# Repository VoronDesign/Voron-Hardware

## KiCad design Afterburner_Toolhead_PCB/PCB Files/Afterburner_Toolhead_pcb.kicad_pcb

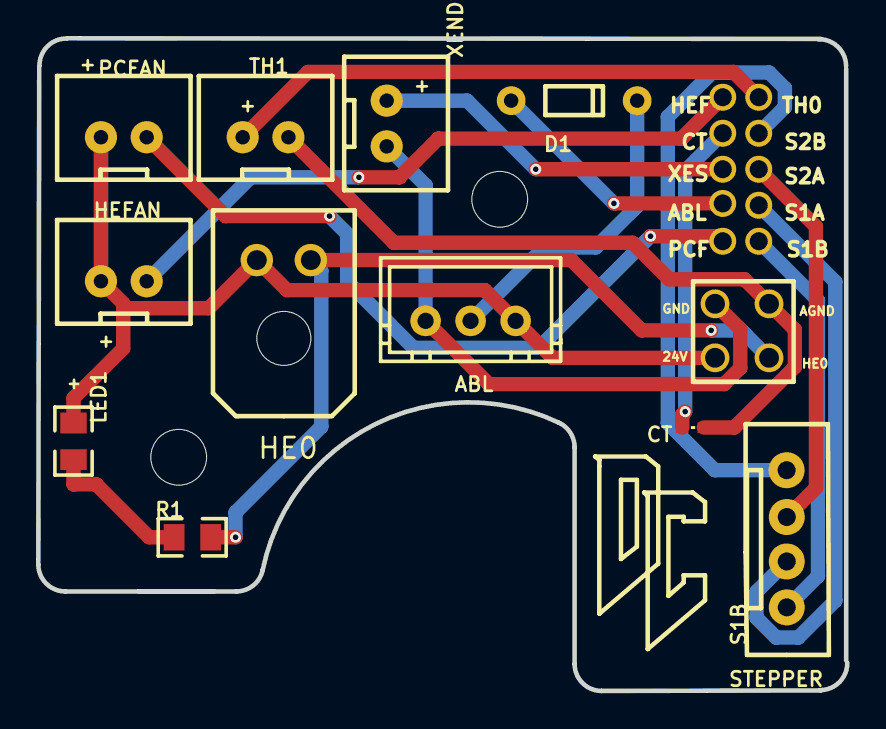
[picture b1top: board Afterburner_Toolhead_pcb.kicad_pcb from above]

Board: 2 copper layers, 44.9 x 36.3 mm, 13 parts (0 on the bottom side), 16 nets.

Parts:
ABL: ABL Sensor (Optional); JST-XH-03-PACKAGE-LONG-PAD
CT: Chamber Temp; 0402
D1: BAT85; DO-34_BD1.6-L3.0-P7.00-D0.6-RD
HE0: MicroFit_1x2; MICROFIT_2X1_WITHHOLE
HEFAN: +; JST-XH-02-ROUND_PAD
J1: MICROFIT-4; MICROFIT_2X2_NOHOLE
LED1: +; 0805-LED
PCFAN: +; JST-XH-02-ROUND_PAD
R1: 1.5K; RESISTOR 0805
STEPPER: S1B; JST-XH04
TH1: +; JST-XH-02-ROUND_PAD
U1: 2x5 2mm pitch; 2MM PITCH PS2 CONT 2X5
XENDSTOP: +; JST-XH-02-ROUND_PAD

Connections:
24V: ABL.1, HE0.2, HEFAN.1, J1.2, LED1.1, PCFAN.1
ABLSIGNALMCU: D1.2, U1.2
ABLSIGNALPROBE: ABL.2, D1.1
AGND: CT.2, J1.3, TH1.2
CHT: CT.1, U1.4
FAN2GND: PCFAN.2, U1.1
GND: ABL.3, J1.4, XENDSTOP.2
HEATER1GND: HE0.1, J1.1, R1.2
HEFANGND: HEFAN.2, U1.5
LED1_2: LED1.2, R1.1
STEPPER1A: STEPPER.3, U1.9
STEPPER1B: STEPPER.4, U1.10
STEPPER2A: STEPPER.2, U1.8
STEPPER2B: STEPPER.1, U1.7
TH1: TH1.1, U1.6
XENDSTOPSIGNAL: U1.3, XENDSTOP.1

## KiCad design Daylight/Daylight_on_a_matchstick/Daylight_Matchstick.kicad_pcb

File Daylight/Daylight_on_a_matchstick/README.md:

# Daylight on a matchstick

12 White leds to accurately illuminate your V0 or other ant-sized printer.

## BOM
| Quantity | Value                         | Package |
|----------|-------------------------------|---------|
|        4 | 100 Ohms Resistor             | 1210    |
|       12 | White LED (4000K, 90+ CRI)    | 2835    |
|        2 | JST-XH (2.54) angled connector| 2pin    |

## Changelog

### V1.0
Initial public release.

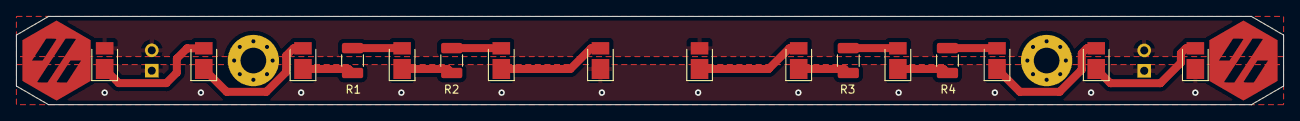
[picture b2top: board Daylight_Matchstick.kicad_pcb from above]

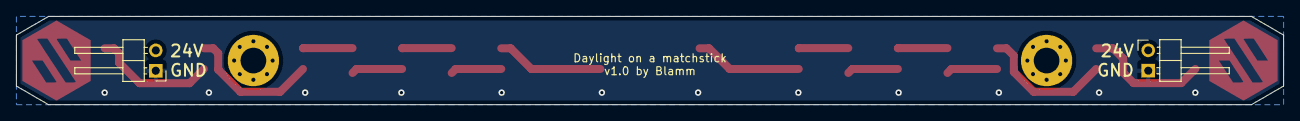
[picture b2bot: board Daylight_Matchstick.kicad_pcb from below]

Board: 2 copper layers, 158.0 x 11.0 mm, 20 parts (2 on the bottom side), 16 nets.

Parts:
D1, D2, D3, D4, D5, D6, D7, D8, D9, D10, D11, D12: LED_ALT; LED_PLCC_2835_Handsoldering
H1, H2: MountingHole; MountingHole_3.2mm_M3_Pad_Via
J1: Conn_01x02_Female; PinHeader_1x02_P2.54mm_Horizontal_mirrored
J2: Conn_01x02_Female; PinHeader_1x02_P2.54mm_Horizontal
R1, R2, R3, R4: 100R 0.5W; R_1210_3225Metric_Pad1.30x2.65mm_HandSolder

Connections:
+24V: D1.2 (A), D7.2 (A), J1.2, J2.2
GND: D6.1 (K), D12.1 (K), J1.1, J2.1
unnamed: D1.1 (K), D2.2 (A)
unnamed: D2.1 (K), D3.2 (A)
unnamed: D3.1 (K), R1.2
unnamed: D4.1 (K), R2.2
unnamed: D4.2 (A), R1.1
unnamed: D5.1 (K), D6.2 (A)
unnamed: D5.2 (A), R2.1
unnamed: D7.1 (K), D8.2 (A)
unnamed: D8.1 (K), R3.2
unnamed: D9.1 (K), R4.2
unnamed: D9.2 (A), R3.1
unnamed: D11.1 (K), D12.2 (A)
unnamed: D10.1 (K), D11.2 (A)
unnamed: D10.2 (A), R4.1

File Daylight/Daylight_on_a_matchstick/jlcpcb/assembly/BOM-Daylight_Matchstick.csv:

Comment,Designator,Footprint,LCSC
100R 0.5W,"R1,R2,R3,R4",R_1210_3225Metric_Pad1.30x2.65mm_HandSolder,C137089
LED_ALT,"D1,D10,D11,D12,D2,D3,D4,D5,D6,D7,D8,D9",LED_PLCC_2835_Handsoldering,C182223
MountingHole,H2,MountingHole_3.2mm_M3_Pad_Via,
MountingHole,H1,MountingHole_3.2mm_M3_Pad_Via,
Conn_01x02_Female,J1,PinHeader_1x02_P2.54mm_Horizontal_mirrored,
Conn_01x02_Female,J2,PinHeader_1x02_P2.54mm_Horizontal,

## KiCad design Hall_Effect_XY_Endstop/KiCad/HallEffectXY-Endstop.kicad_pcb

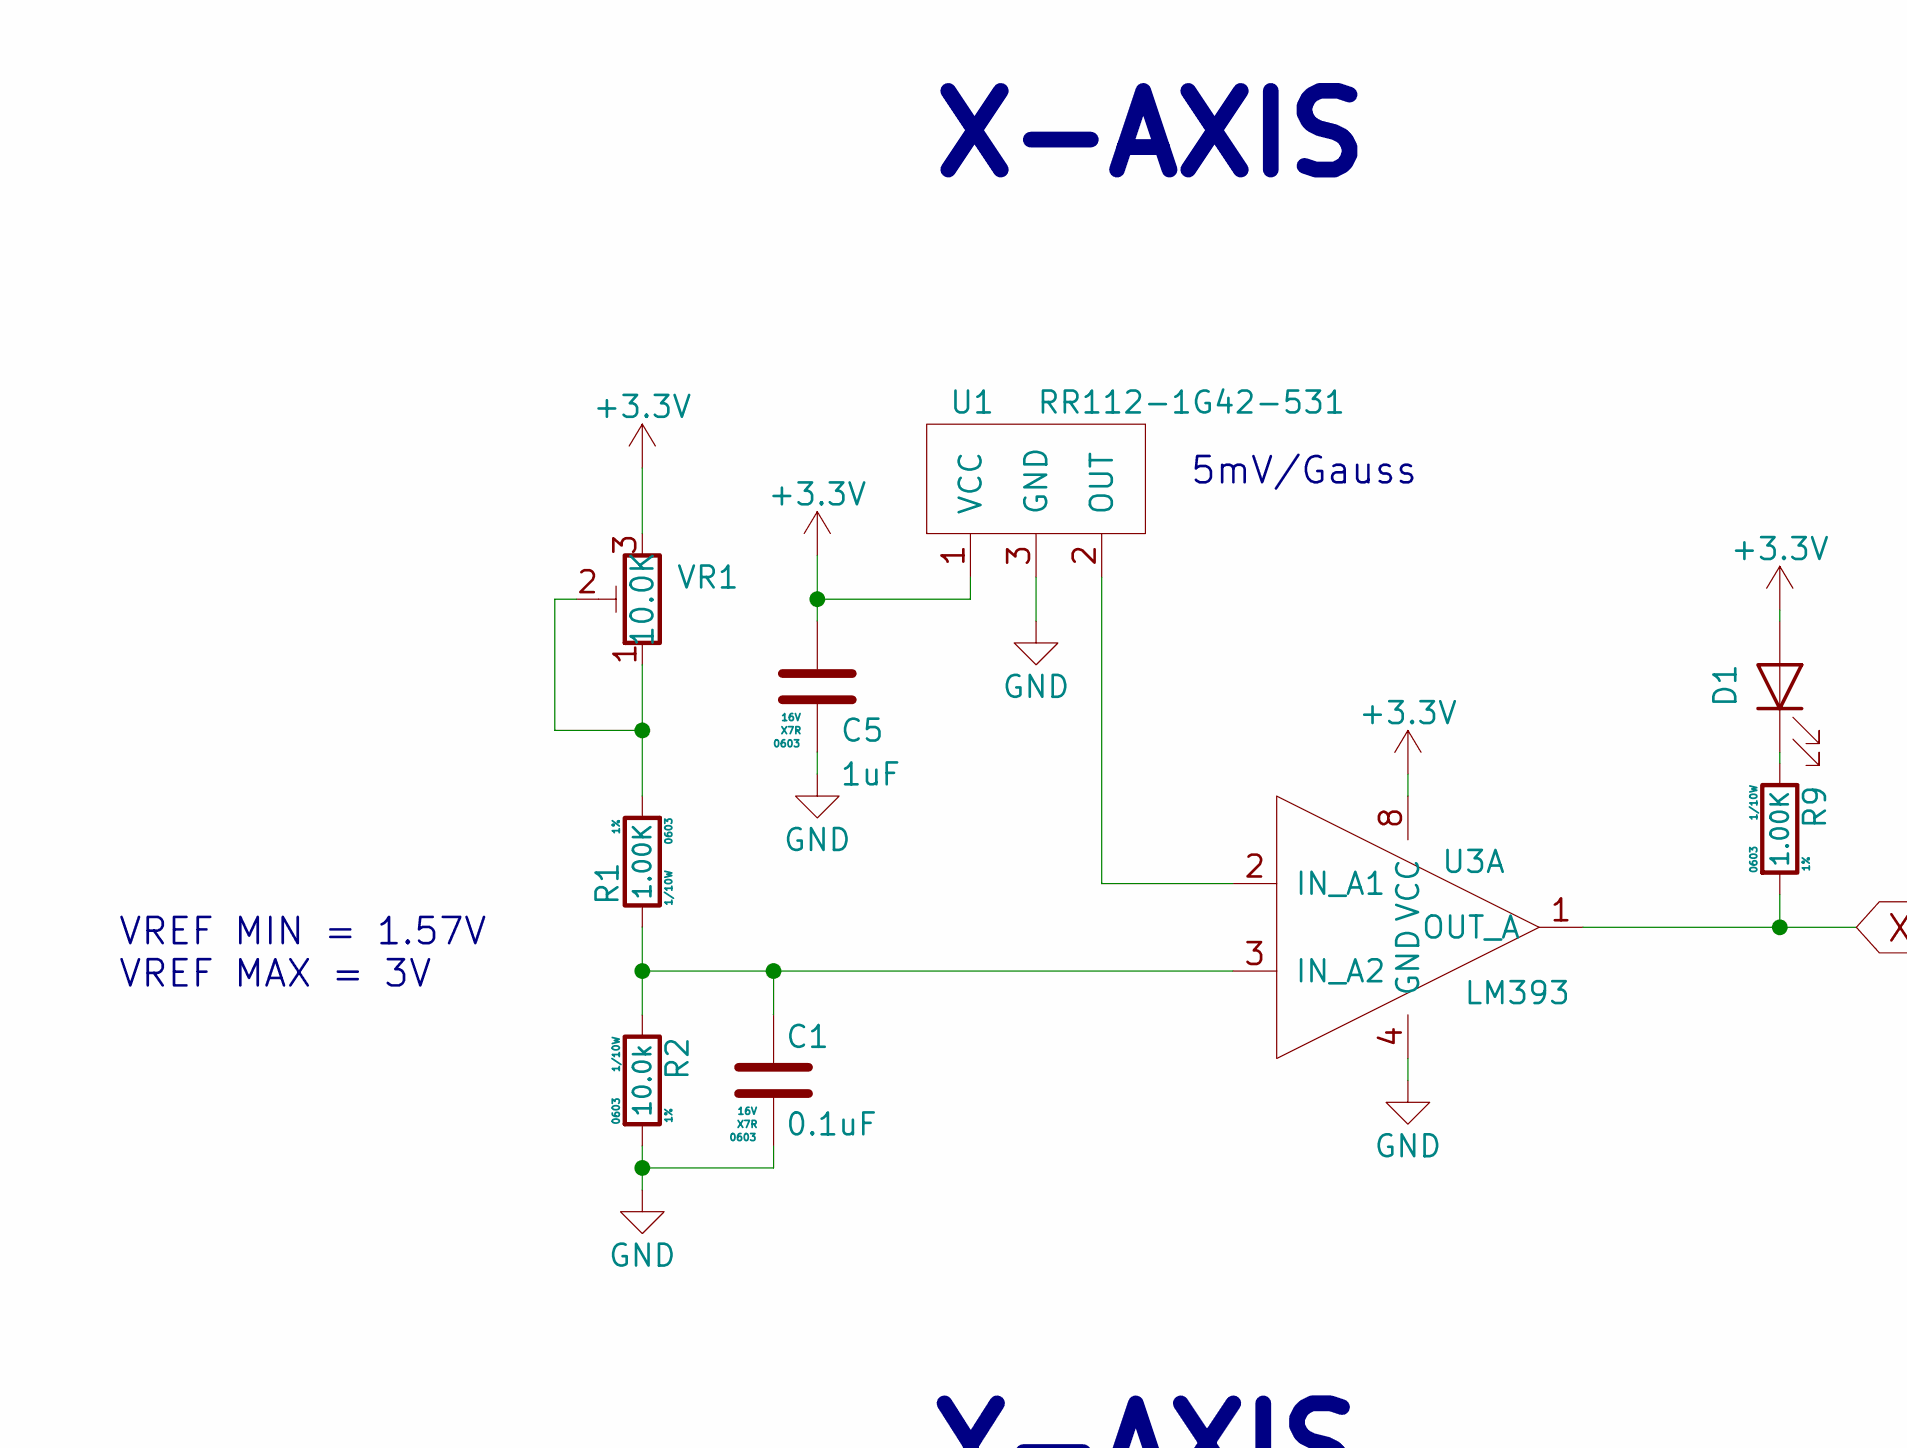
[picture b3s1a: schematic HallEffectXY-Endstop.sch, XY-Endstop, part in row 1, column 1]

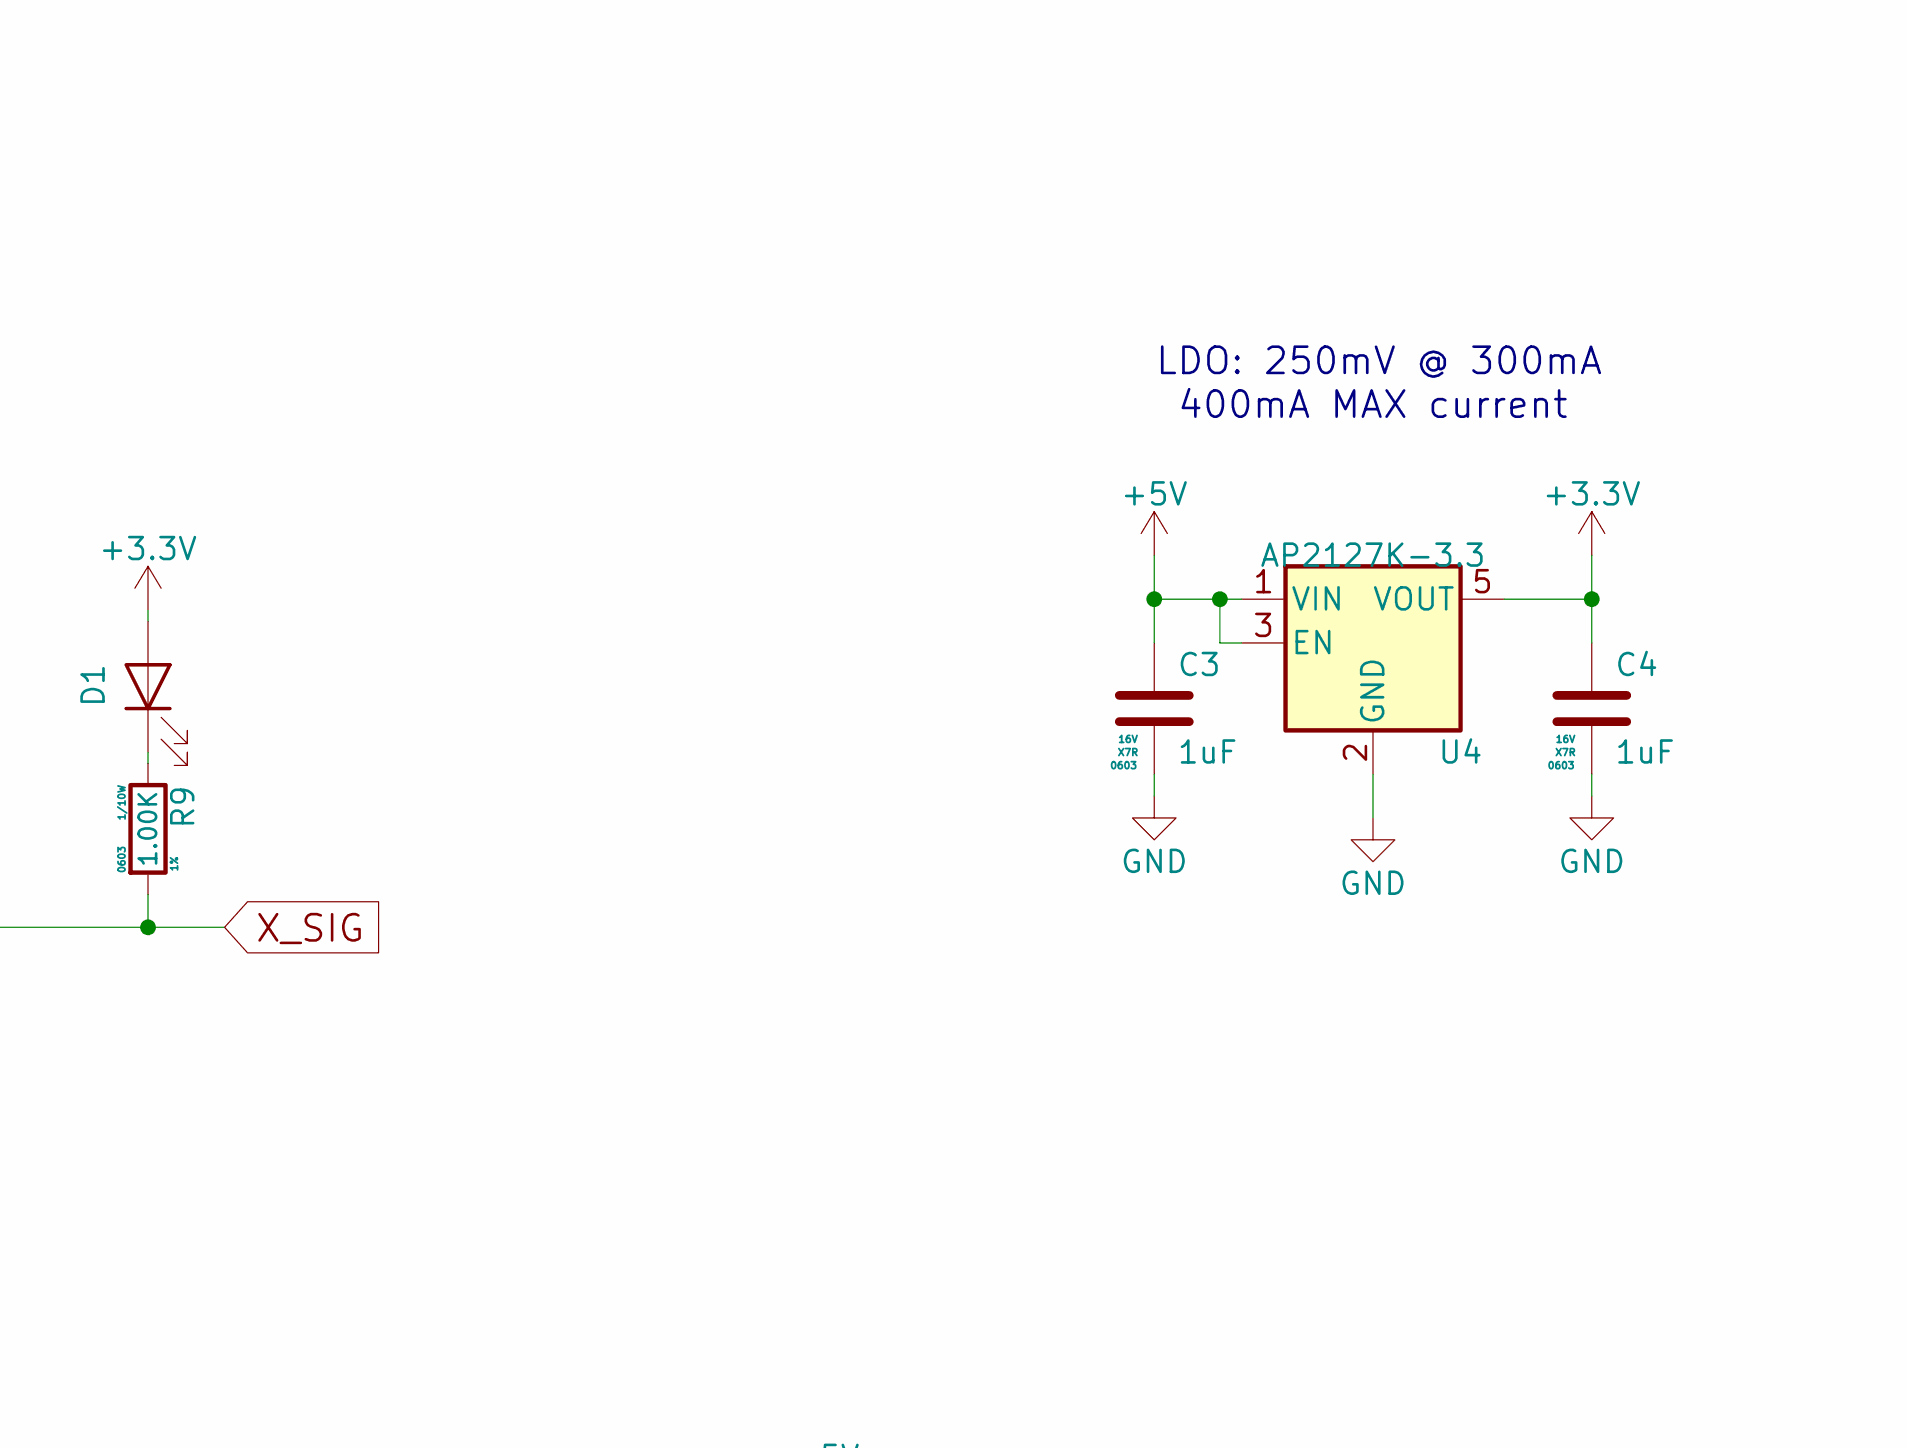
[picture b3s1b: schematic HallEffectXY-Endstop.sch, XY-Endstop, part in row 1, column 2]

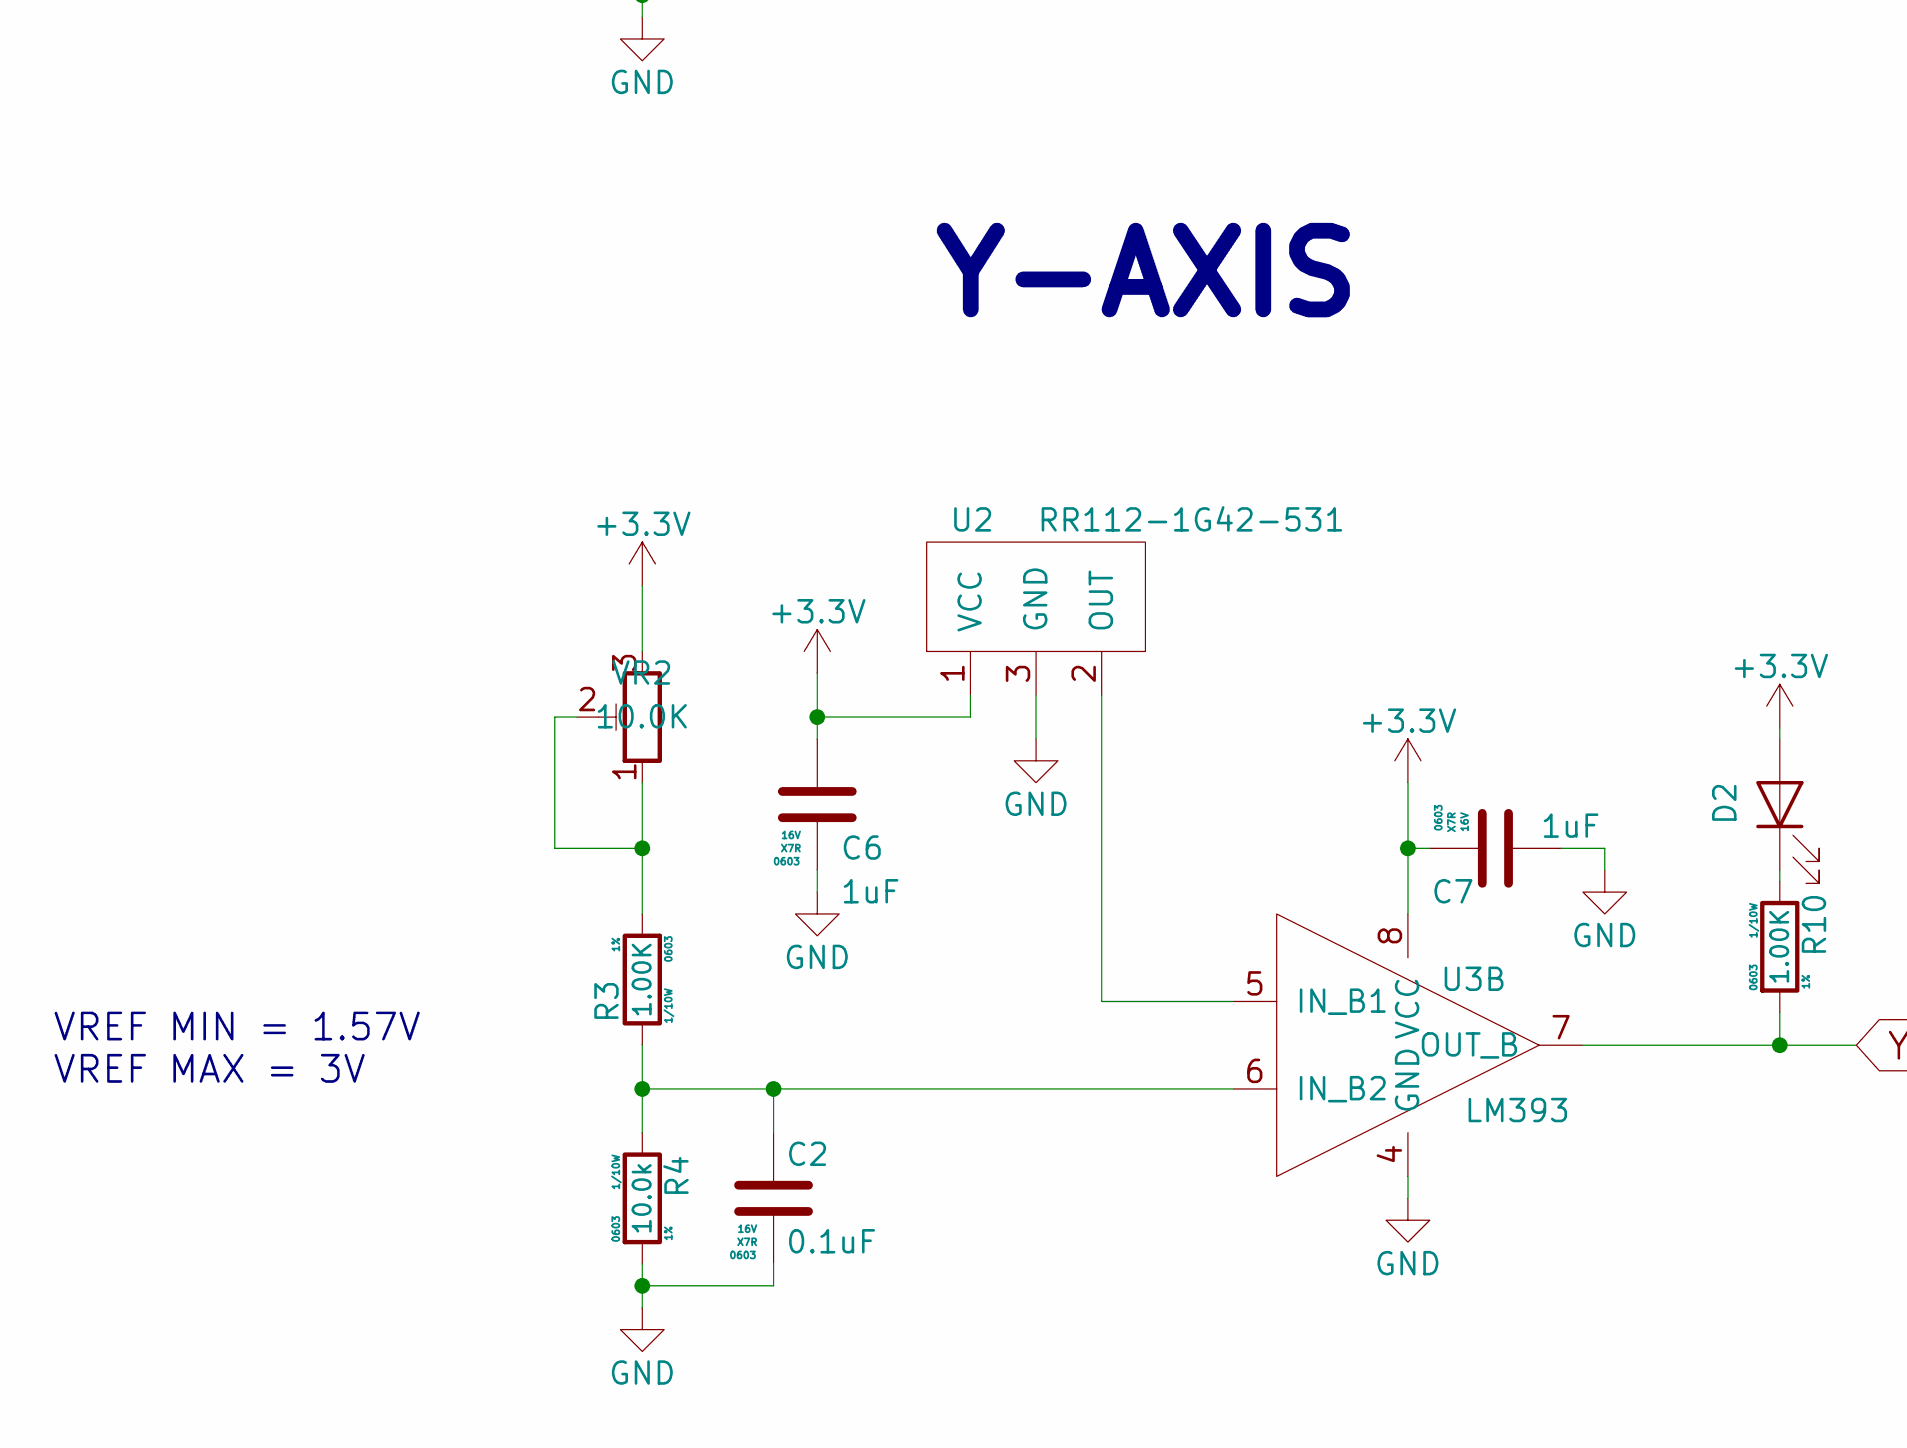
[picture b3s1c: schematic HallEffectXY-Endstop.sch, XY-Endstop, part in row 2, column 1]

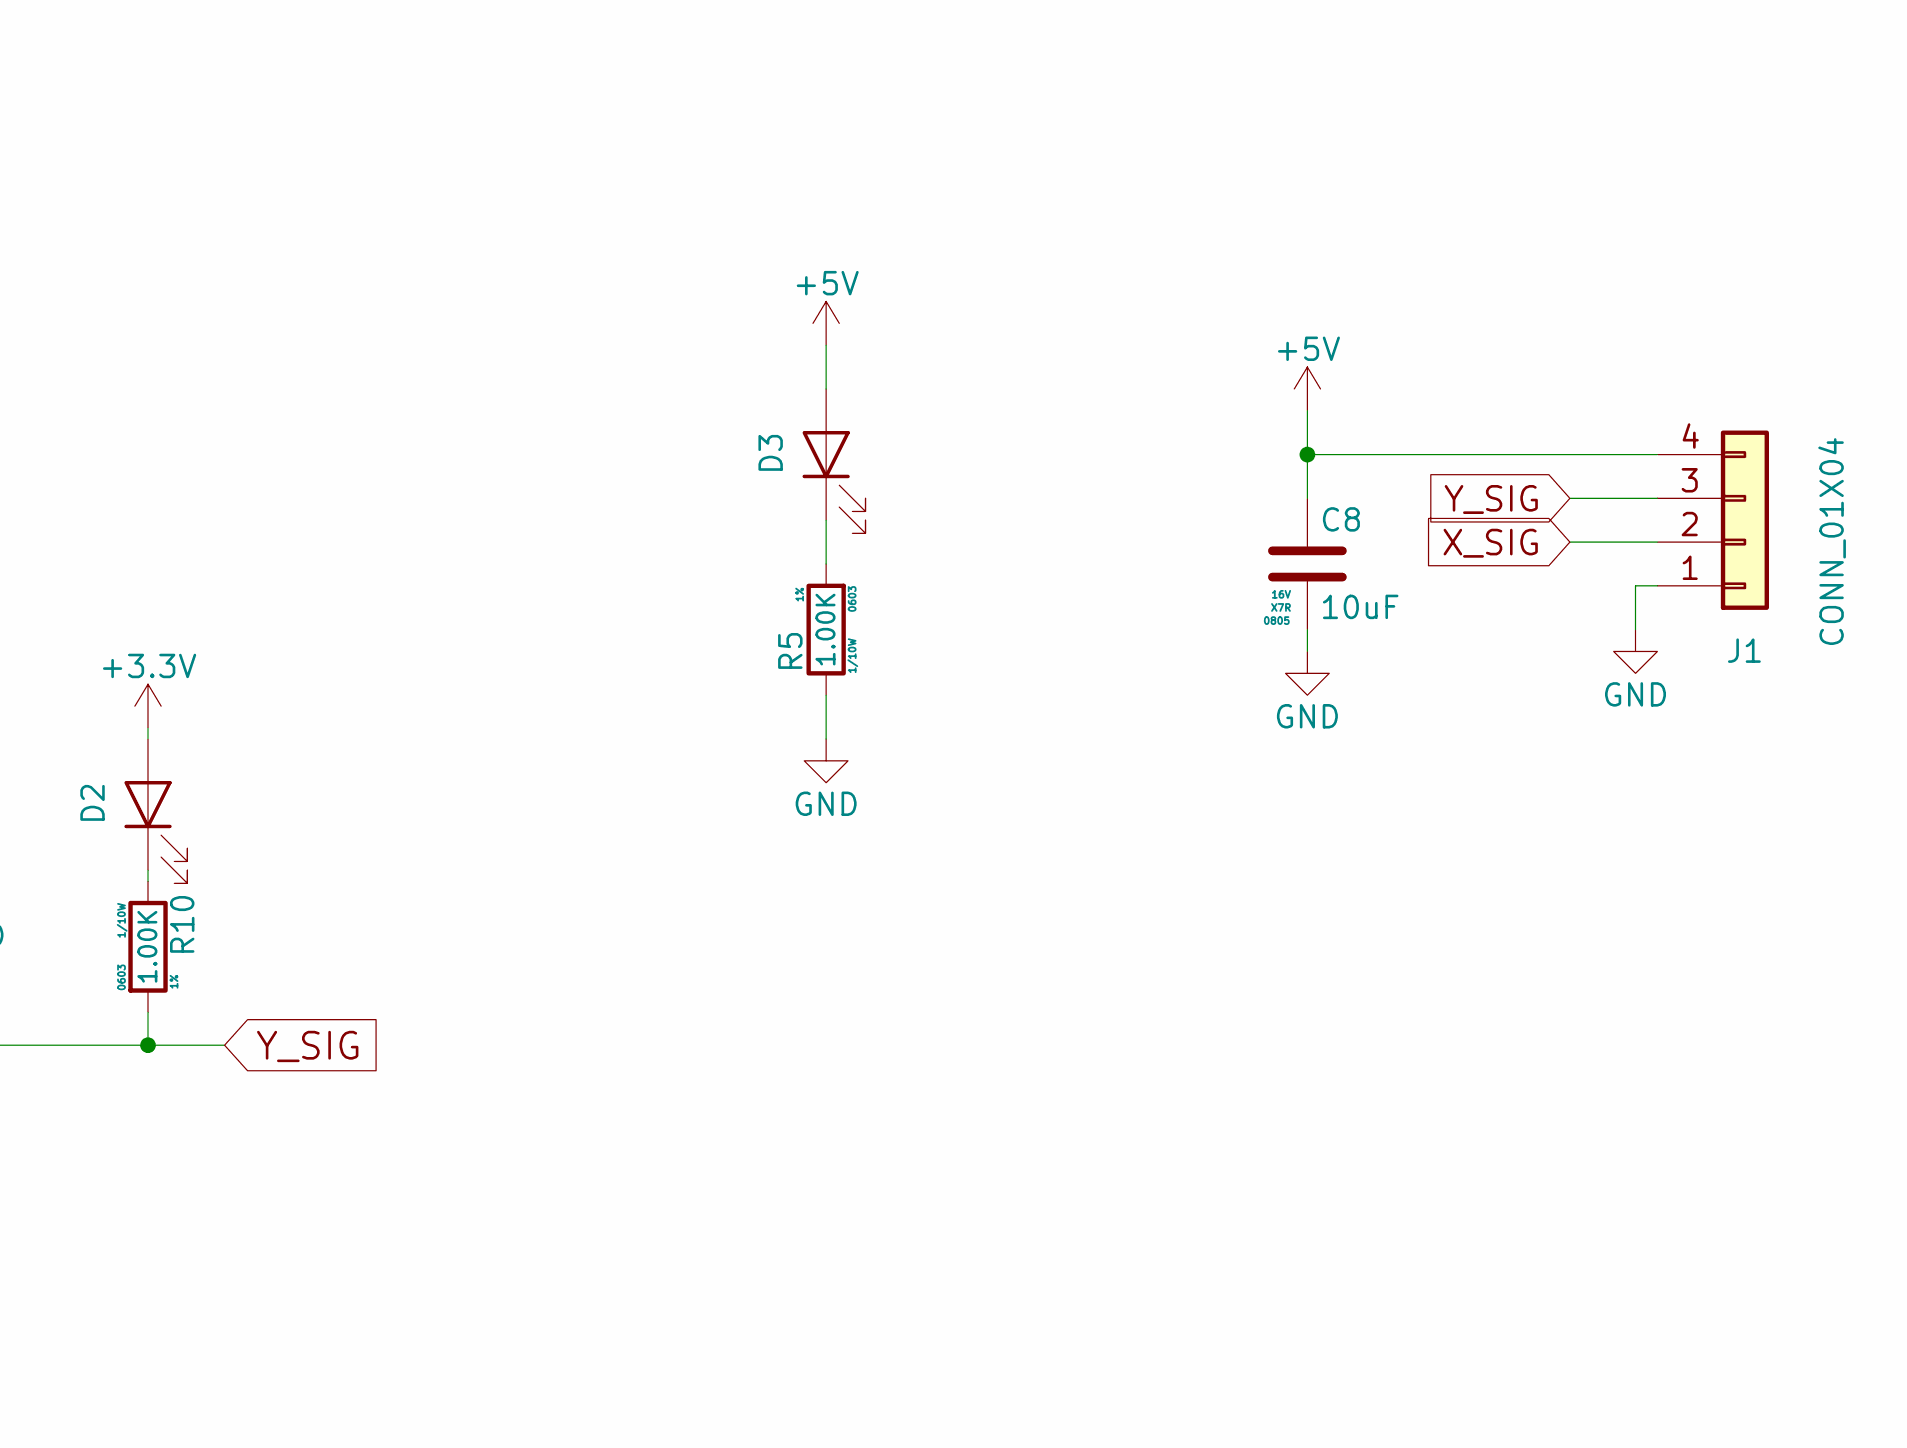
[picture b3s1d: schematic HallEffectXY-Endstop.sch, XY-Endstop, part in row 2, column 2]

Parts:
C1, C2: 0.1uF; C_0805_2012Metric; Voltage 16V; Manufacture P/N CC0603KRX7R7BB104; Digi-Key 311-1088-1-ND
C3, C4, C5, C6, C7: 1uF; C_0805_2012Metric; Voltage 16V; Manufacture P/N EMK107B7105KA-T; Digi-Key 587-1241-1-ND
C8: 10uF; C_0805_2012Metric; Voltage 16V; Manufacture P/N CL21A106KOQNNNG; Digi-Key 1276-6455-1-ND
D1, D2, D3: LED_0805; LED_0805_2012Metric; Manufacture P/N LS R976-NR-1; Digi-Key 475-1278-1-ND
J1: CONN_01X04; PinHeader_1x04_P2.54mm_Vertical; Manufacture P/N 0705530003; Digi-Key WM4902-ND
R1, R5: 1.00K; R_0805_2012Metric; Tolerance 1%; Manufacture P/N RC0402FR-071KL; Digi-Key 311-1.00KLRCT-ND
R2, R4: 10.0k; R_0805_2012Metric; Tolerance 1%; Manufacture P/N RC0603FR-0710KL; Digi-Key 311-10.0KHRCT-ND
R3, R9, R10: 1.00K; R_0805_2012Metric; Tolerance 1%; Manufacture P/N RC0603FR-071KL; Digi-Key 311-1.00KHRCT-ND
U1, U2: RR112-1G42-531; SOT-23; Manufacture P/N SS39ET; Digi-Key 306-RR112-1G42-531CT-ND
U3: LM393; SOIC-8_3.9x4.9mm_P1.27mm; Manufacture P/N LM393M; Digi-Key LM393MFS-ND
U4: AP2127K-3.3; SOT-23-5; Manufacture P/N AP2210N-3.3TRG1; Digi-Key AP2210N-3.3TRG1DICT-ND
VR1, VR2: 10.0K; CT6EP103; Manufacture P/N CT6EP103; Digi-Key CT6EP103-ND

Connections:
+3V3: C4.1, C5.1, C6.1, C7.2, D1.2 (A), D2.2 (A), U1.1 (VCC), U2.1 (VCC), U3.8 (VCC), U4.5 (VOUT), VR1.3, VR2.3
+5V: C3.1, C8.1, D3.2 (A), J1.4, U4.1 (VIN), U4.3 (EN)
GND: C1.2, C2.2, C3.2, C4.2, C5.2, C6.2, C7.1, C8.2, J1.1, R2.2, R4.2, R5.1, U1.3 (GND), U2.3 (GND), U3.4 (GND), U4.2 (GND)
unnamed: C1.1, R1.1, R2.1, U3.3 (IN_A2)
unnamed: C2.1, R3.1, R4.1, U3.6 (IN_B2)
unnamed: D1.1 (K), R9.1
unnamed: D2.1 (K), R10.1
unnamed: D3.1 (K), R5.2
unnamed: R1.2, VR1.1, VR1.2
unnamed: R3.2, VR2.1, VR2.2
unnamed: U1.2 (OUT), U3.2 (IN_A1)
unnamed: U2.2 (OUT), U3.5 (IN_B1)
X_SIG: J1.2, R9.2, U3.1 (OUT_A)
Y_SIG: J1.3, R10.2, U3.7 (OUT_B)

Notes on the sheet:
VREF MIN = 1.57V VREF MAX = 3V
X-AXIS
Y-AXIS
LDO: 250mV @ 300mA
400mA MAX current
5mV/Gauss

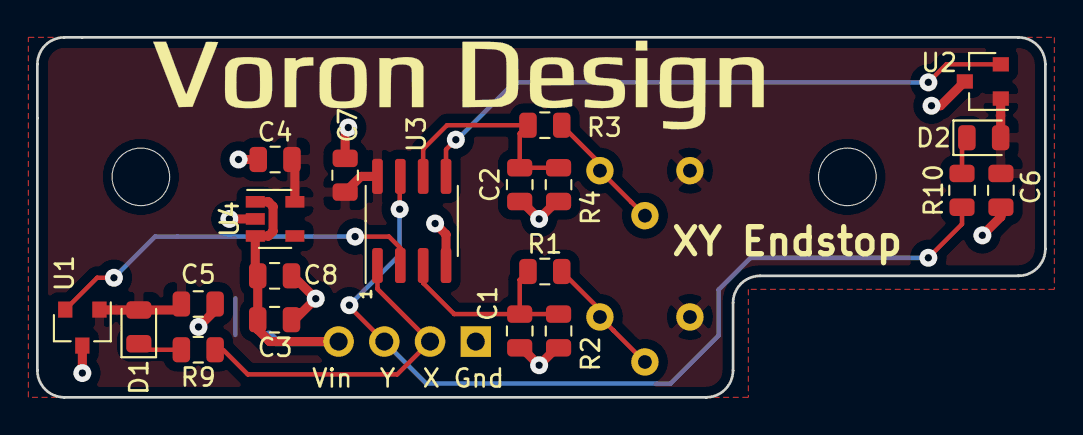
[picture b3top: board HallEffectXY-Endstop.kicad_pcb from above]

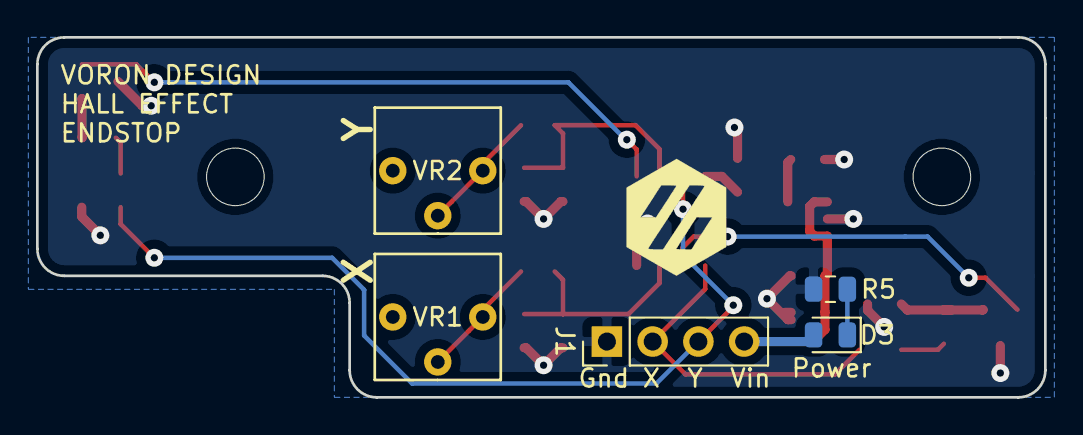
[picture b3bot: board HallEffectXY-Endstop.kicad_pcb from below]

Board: 2 copper layers, 56.0 x 20.0 mm, 25 parts (5 on the bottom side), 14 nets.

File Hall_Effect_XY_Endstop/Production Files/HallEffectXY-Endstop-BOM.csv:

Comment,Designator,Footprint,LCSC
0.1uF,"C2,C1",HallEffect_XY:C_0805_2012Metric,C49678
1uF,"C7,C6,C5,C3,C4",HallEffect_XY:C_0805_2012Metric,C28323
10uF,C8,HallEffect_XY:C_0805_2012Metric,C15850
LED_0805,"D2,D1,D3",HallEffect_XY:LED_0805_2012Metric,C84256
CONN_01X04,J1,HallEffect_XY:PinHeader_1x04_P2.54mm_Vertical,C225490
1.00K,"R1,R3,R9,R10,R5",HallEffect_XY:R_0805_2012Metric,C17513
10.0k,"R4,R2",HallEffect_XY:R_0805_2012Metric,C17414
SS39ET,"U2,U1",HallEffect_XY:SOT-23,C126669
LM393,U3,HallEffect_XY:SOIC-8_3.9x4.9mm_P1.27mm,C7955
AP2127K-3.3,U4,HallEffect_XY:SOT-23-5,C156285
10.0K,"VR2,VR1",HallEffect_XY:CT6EP103,C118956

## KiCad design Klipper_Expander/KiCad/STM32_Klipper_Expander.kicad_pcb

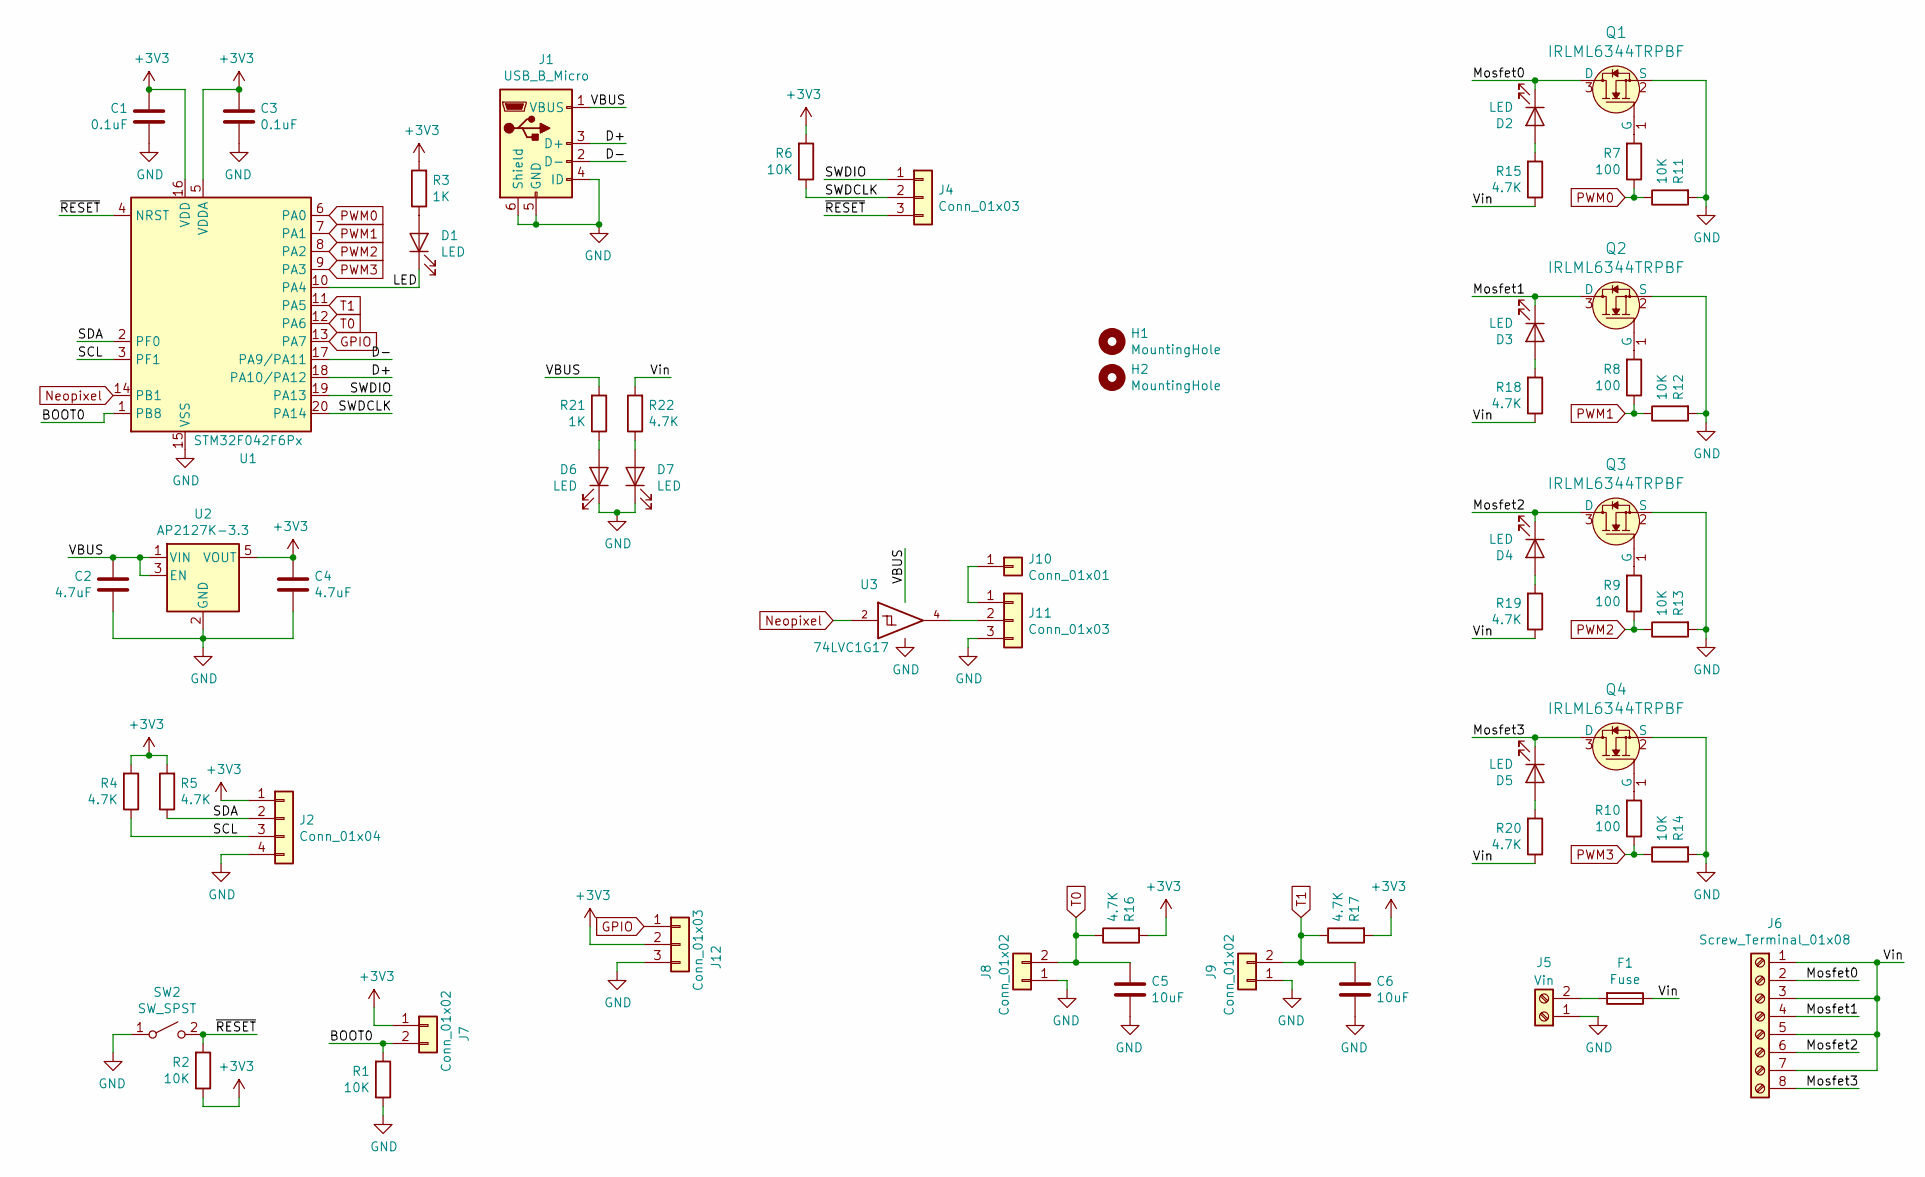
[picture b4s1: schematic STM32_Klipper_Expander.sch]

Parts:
C1, C3: 0.1uF; C_0805_2012Metric; MPN CC0805KRX7R9BB104; LCSC C49678
C2, C4: 4.7uF; C_0805_2012Metric; MPN CC0805KKX5R8BB475; LCSC C1779
C5, C6: 10uF; C_0805_2012Metric; MPN CC0805ZKY5V6BB106; LCSC C15850
D1, D2, D3, D4, D5, D6, D7: LED; LED_0805_2012Metric; MPN 17-215SURC/S530-A2/TR8; LCSC C84256
F1: Fuse; 3544-2_FuseHolder
H1, H2: MountingHole; MountingHole_3.2mm_M3
J1: USB_B_Micro; Molex-105017-0001-USBMicroB; MPN 1050170001
J2: Conn_01x04; PinHeader_1x04_P2.54mm_Vertical
J4, J11, J12: Conn_01x03; PinHeader_1x03_P2.54mm_Vertical
J5: Vin; 1x02_ScrewTerminal_Phoenix
J6: Screw_Terminal_01x08; 1x08_ScrewTerminal_Phoenix
J7, J8, J9: Conn_01x02; PinHeader_1x02_P2.54mm_Vertical
J10: Conn_01x01; PinHeader_1x01_P2.54mm_Vertical
Q1, Q2, Q3, Q4: IRLML6344TRPBF; SOT-23; MPN IRLML6344TRPBF; Digi-Key_PN IRLML6344TRPBFCT-ND
R1, R2, R6, R11, R12, R13, R14: 10K; R_0805_2012Metric; MPN RC0805JR-0710KL; LCSC C17414
R3, R21: 1K; R_0805_2012Metric; MPN RC0805JR-071KL; LCSC C17513
R4, R5, R15, R16, R17, R18, R19, R20, R22: 4.7K; R_0805_2012Metric; MPN RC0805JR-074K7L; LCSC C17673
R7, R8, R9, R10: 100; R_0805_2012Metric; MPN RC0805JR-07100RL; LCSC C17408
SW2: SW_SPST; 2PinTactileButton
U1: STM32F042F6Px; TSSOP-20_4.4x6.5mm_P0.65mm; MPN STM32F042F6P6; LCSC C81000
U2: AP2127K-3.3; SOT-23-5; MPN AP2127K-3.3TRG1; LCSC C156285
U3: 74LVC1G17; SOT-753; LCSC C6076

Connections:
+3V3: C1.2, C3.2, C4.2, J2.1, J7.1, J12.2, R2.1, R3.2, R4.2, R5.2, R6.2, R16.2, R17.2, U1.5 (VDDA), U1.16 (VDD), U2.5 (VOUT)
/BOOT0: J7.2, R1.2, U1.1 (PB8)
/D+: J1.3 (D+), U1.18 (PA10/PA12)
/D-: J1.2 (D-), U1.17 (PA9/PA11)
/LED: D1.1 (K), U1.10 (PA4)
/Mosfet0: D2.1 (K), J6.2, Q1.3 (D)
/Mosfet1: D3.1 (K), J6.4, Q2.3 (D)
/Mosfet2: D4.1 (K), J6.6, Q3.3 (D)
/Mosfet3: D5.1 (K), J6.8, Q4.3 (D)
/SCL: J2.3, R4.1, U1.3 (PF1)
/SDA: J2.2, R5.1, U1.2 (PF0)
/SWDCLK: J4.2, R6.1, U1.20 (PA14)
/SWDIO: J4.1, U1.19 (PA13)
/Vin: F1.1, J6.1, J6.3, J6.5, J6.7, R15.1, R18.1, R19.1, R20.1, R22.2
/~RESET: J4.3, R2.2, SW2.2 (B), U1.4 (NRST)
GND: C1.1, C2.1, C3.1, C4.1, C5.1, C6.1, D6.1 (K), D7.1 (K), J1.4 (ID), J1.5 (GND), J1.6 (Shield), J2.4, J5.1, J8.1, J9.1, J11.3, J12.3, Q1.2 (S), Q2.2 (S), Q3.2 (S), Q4.2 (S), R1.1, R11.2, R12.2, R13.2, R14.2, SW2.1 (A), U1.15 (VSS), U2.2 (GND), U3.3 (GND)
GPIO: J12.1, U1.13 (PA7)
Neopixel: U1.14 (PB1), U3.2
unnamed: D1.2 (A), R3.1
unnamed: D2.2 (A), R15.2
unnamed: D3.2 (A), R18.2
unnamed: D4.2 (A), R19.2
unnamed: D5.2 (A), R20.2
unnamed: D6.2 (A), R21.1
unnamed: D7.2 (A), R22.1
unnamed: F1.2, J5.2
unnamed: J10.1, J11.1
unnamed: J11.2, U3.4
unnamed: Q1.1 (G), R7.2
unnamed: Q2.1 (G), R8.2
unnamed: Q3.1 (G), R9.2
unnamed: Q4.1 (G), R10.2
PWM0: R7.1, R11.1, U1.6 (PA0)
PWM1: R8.1, R12.1, U1.7 (PA1)
PWM2: R9.1, R13.1, U1.8 (PA2)
PWM3: R10.1, R14.1, U1.9 (PA3)
T0: C5.2, J8.2, R16.1, U1.12 (PA6)
T1: C6.2, J9.2, R17.1, U1.11 (PA5)
VCC: C2.2, J1.1 (VBUS), R21.2, U2.1 (VIN), U2.3 (EN), U3.5 (VCC)

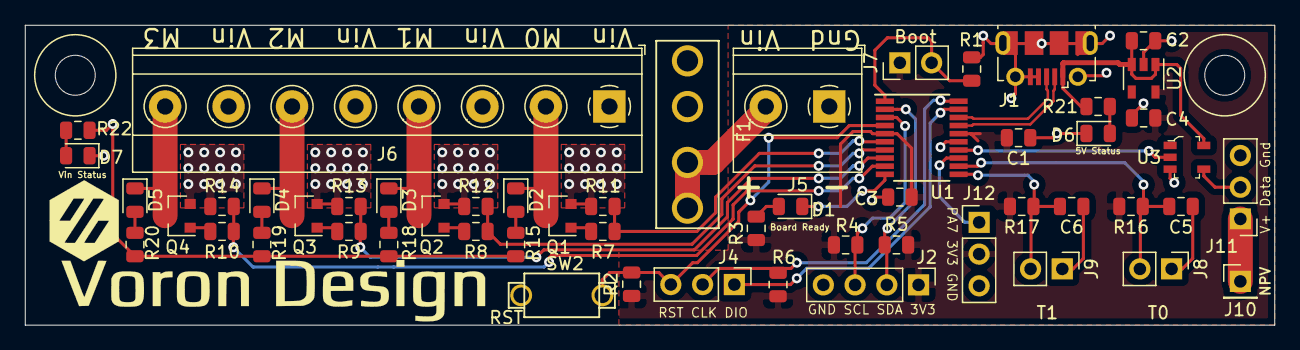
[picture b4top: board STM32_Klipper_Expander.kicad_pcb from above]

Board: 2 copper layers, 100.0 x 24.0 mm, 57 parts (0 on the bottom side), 39 nets.

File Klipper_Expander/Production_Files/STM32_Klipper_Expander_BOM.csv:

Comment,Qty,5 boards,Designator,MPN,Digikey PN,Footprint,LCSC
0.1uF,2,10,"C1,C3",CC0805KRX7R9BB104,311-1140-1-ND,0805,C49678
4.7uF,2,10,"C4,C2",CC0805KKX5R8BB475,311-1871-1-ND,0805,C1779
10uF,2,10,"C5,C6",CC0805ZKY5V6BB106 ,311-1355-1-ND,0805,C15850
LED,1,5,D1,17-215SURC/S530-A2/TR8 ,732-4984-1-ND,0805,C84256
Fuse,1,5,F1,?3544-2?,36-3544-2-ND,TRA_KiCad_Footprints:3544-2_FuseHolder,
MountingHole,2,10,"H1,H2",,,MountingHole:MountingHole_3.2mm_M3,
USB_B_Micro,1,5,J1,1050170001?,WM1399CT-ND,TRA_KiCad_Footprints:Molex-105017-0001-USBMicroB,
Conn_01x01,1,5,J10,PH1-01-UA,2057-PH1-01-UA-ND,Connector_PinHeader_2.54mm:PinHeader_1x01_P2.54mm_Vertical,
Conn_01x04,1,5,J2,61300411121,732-5317-ND,Connector_PinHeader_2.54mm:PinHeader_1x04_P2.54mm_Vertical,
Conn_01x03,2,10,"J4,J11",61300311121,732-5316-ND,Connector_PinHeader_2.54mm:PinHeader_1x03_P2.54mm_Vertical,
Vin,1,5,J5,1715721,277-1263-ND,TRA_KiCad_Footprints:1x02_ScrewTerminal_Phoenix,
Screw_Terminal_01x08,1,5,J6,1715789,277-1266-ND,"TRA_KiCad_Footprints:TerminalBlock_Phoenix_MKDS-1,5-8-5.08_1x08_P5.08mm_Horizontal",
Conn_01x02,2,10,"J7,J12",61300211121,732-5315-ND,Connector_PinHeader_2.54mm:PinHeader_1x02_P2.54mm_Vertical,
Conn_01x02,2,10,"J8,J9",B2B-XH-A(LF)(SN),455-2247-ND,Connector_JST:JST_XH_B02B-XH-A_1x02_P2.50mm_Vertical,
IRLML6344TRPBF,4,20,"Q1,Q4,Q3,Q2",IRLML6344TRPBF,IRLML6344TRPBFCT-ND,Package_TO_SOT_SMD:SOT-23,C20917
10K,9,45,"R2,R1,R16,R17,R14,R13,R12,R11,R6",RC0805JR-0710KL,311-10KARCT-ND,0805,C17414
1K,1,5,R3,RC0805JR-071KL,311-1.0KARCT-ND,0805,C17513
4.7K,2,10,"R5,R4",RC0805JR-074K7L,311-4.7KARCT-ND,0805,C17673
100,4,20,"R7,R8,R10,R9",RC0805JR-07100RL,311-100ARCT-ND,0805,C17408
SW_SPST,1,5,SW2,1825966-1,450-1665-ND,TRA_KiCad_Footprints:2PinTactileButton,
STM32F042F6Px,1,5,U1,STM32F042F6P6,497-17344-ND,TSSOP-20,C81000
AP2127K-3.3,1,5,U2,AP2127K-3.3TRG1,AP2127K-3.3TRG1DICT-ND,SOT-23-5,C156285
74LVC1G17,1,5,U3,74LVC1G17SE-7,74LVC1G17SE-7CT-ND,SOT-353,C124293
